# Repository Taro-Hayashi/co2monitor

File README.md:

# CO2モニター自作キット ビルドガイド
- [キット内容](#キット内容)
- [はんだ付け](#はんだ付け)
- [組み立て](#組み立て)
- [その他](#その他)

## キット内容
 
||部品名|数||
|-|-|-|-|
|1|メインボード|1||
|2|トッププレート|1||
|3|ボトムプレート|1||
|4|スタンド|1||
|5|スペーサー（短）|2|M2 6mm|
|6|スペーサー（長）|4|M2 9mm|
|7|ねじ|8|M2|
|8|リセットスイッチ|1||
|9|LED|1|SK6812MINI-E|
|10|OLED|1|SSD1306|
|11|キースイッチ|1||
|12|キーキャップ|1||
|13|ゴム足|8||

### キット以外に必要なもの
|部品名|数||
|-|-|-|
|Pro Micro（Micro-B/Type-C）|1||
|MG-812使用CO2ガスセンサアンプキット|1|[秋月電子通商](https://akizukidenshi.com/catalog/g/gK-16446/)|
|USB ケーブル|1|各種キーボードショップ、100円均一など|

## はんだ付け
LEDをメインボード裏面にはんだ付けします。欠けがある方向と折れ曲がった白線が一致するようにしてください。

リセットスイッチを裏面から差し込みはんだ付けします。
 
Pro Microを付属のピンヘッダーで取り付けて両面をはんだ付けします。
 
付属、もしくはお好みのキースイッチを表面に差し込みはんだ付けします。
 
MG-812使用CO2ガスセンサアンプキットを組み立てます。

> [!IMPORTANT] 
> 熱に弱い部品が使われているので熱しすぎないようにしてください。

OLEDはピンヘッダがはんだ付けされた状態でパッケージングされています。保護フィルムを剥がします。
 
２カ所にゴム足を貼ります。　　
 
OLEDとMG-812をメインボードにはんだ付けします。
 
動作の確認をするためにUSBケーブルでPCと接続しましょう。

### 動作テスト
ファームウェアを書き込みます。こちらのファイルをダウンロードしてください。
- [tarohayashi_co2monitor_default.hex](https://github.com/Taro-Hayashi/co2monitor/releases/latest/download/tarohayashi_co2monitor_default.hex)

こちらのサイトにGoogle ChromeでアクセスするとWebブラウザ経由で書き込むことができます。
- https://sekigon-gonnoc.github.io/promicro-web-updater/index.html

もしくはQMK Toolboxを使ってファームウェアを書き込んでください。
- [QMK Toolboxを使ったファームウェア更新方法](firmware.md)

少し待ちディスプレイに数字が表示され、キーを押してLEDの発光方法が変わればはんだ付けに成功しています。
 
> [!NOTE] 
> 数値が8888で固定されてしまうことがあります。これはMG-812にエージングが必要な個体が存在するためです。数日起動したままにすると徐々に性能が発揮されるようになります。

## 組み立て
USBケーブルを抜いてプレートを組付けます。  
メインボードにスペーサーを取り付けます。
 
表面の4箇所にスペーサー（長）を差し込み、裏面は写真のようにネジとスペーサー（短）で止めます。
 
トッププレートをねじ止めします。
 
ボトムプレートをねじで取り付けてゴム足を貼り付けたら完成です。

お好みでスタンドをお使いください。
 
USBケーブルをPCやUSB充電器などに接続して好きなところに置いてください。  

## 機能
スイッチを押すとLEDの光り方が切り替わります。  

|発光モード||
|-|-|
|GRADATION|ppmでLEDの色が段階的に変わります|
|THRESHOLD|設定された濃度になったら赤く光ります（初期設定：2000ppm)|
|OFF|LEDを光らなくします。|

また、スイッチを1秒以上押し続けてから離すと内部の状態をリセットできます。  
リセットは3日ごとに自動的にかかるようにしています。

## ご注意
- CO2センサーは発熱します。触り続けると低温やけどを引き起こすのでご注意ください。  
- 表示される数値は正確な濃度ではありません。換気された部屋を400ppmとした目安の値です。  
- PCのUSBからの電力供給は負荷やスリープなどで安定しないので動作確認後はUSB充電器への接続がおすすめです。  

### ファームウェアのコード
https://github.com/Taro-Hayashi/qmk_firmware/tree/tarohayashi/keyboards/tarohayashi/co2monitor

### 販売サイト
- BOOTH: https://tarohayashi.booth.pm/items/4500742

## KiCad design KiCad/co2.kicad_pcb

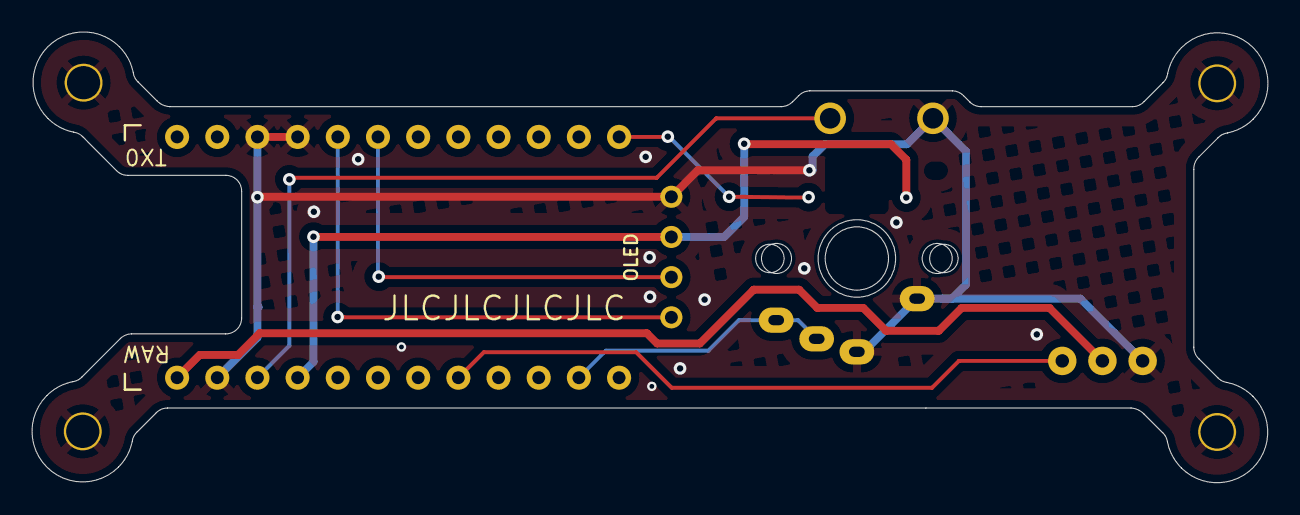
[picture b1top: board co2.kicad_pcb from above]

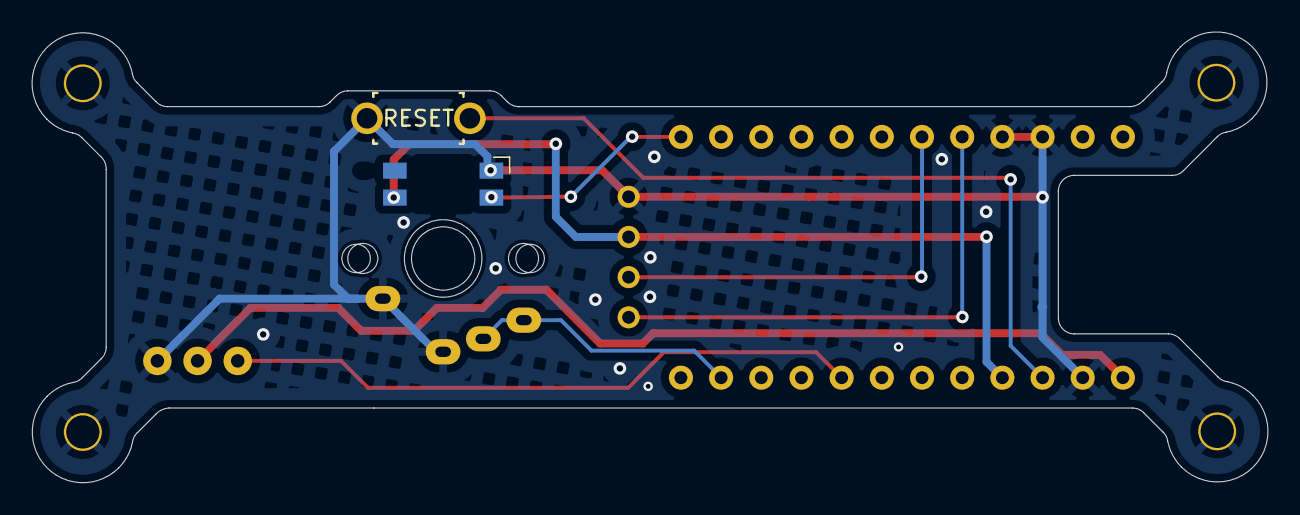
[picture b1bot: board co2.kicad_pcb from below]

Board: 2 copper layers, 78.1 x 28.5 mm, 11 parts (2 on the bottom side), 9 nets.

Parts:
BL1: YS-SK6812MINI-E; LED_SK6812MINI-E_Backlight
H1, H2, H3, H4: Hole; Hole_2mm_M2_PTH
OL1: OLED
RST1: ResetSW
SW1: SW_PUSH; CherryMX_1u
SW2: SW_PUSH; ChocV2_1u
U1: ProMicro
co1: MG812; DIP-MG812

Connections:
5v: U1.24 (RAW), co1.2 (5V)
GND: BL1.3 (VSS), H1.1, H2.1, H3.1, H4.1, OL1.4 (GND), RST1.2, SW1.2, SW2.2, U1.3 (GND), U1.4 (GND), U1.23 (GND), co1.3 (GND)
SCL: OL1.2 (SCL), U1.6 (3/D0/SCL)
SDA: OL1.1 (SDA), U1.5 (2/D1/SDA)
VCC: BL1.1 (VDD), OL1.3 (VCC), U1.21 (VCC)
co2: U1.17 (F7/A0), co1.1 (OUT)
led: BL1.4 (DIN), U1.12 (9/B5)
reset: RST1.1, U1.22 (RST)
sw: SW1.1, SW2.1, U1.14 (B2/16)

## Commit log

2023-02-19 code
2023-02-22 change directory
2026-05-24 Add hardware design files
2026-05-24 Add QMK firmware files
